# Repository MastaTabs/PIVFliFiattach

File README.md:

# PIV FlickerFixer attachment

This is a recreation from original data of the small snap off PCB of the PicassoIV (PIV)
Amiga RTG graphics card.
I created this because often cards seem to be sold without this PCB and then the FlickerFixer/ScanDoubler
of the card cannot be used.

This is a four layer PCB.

### License
The "PIV FlickerFixer attachment" documentation, including the design itself, is copyright © MastaTabs (Tobias Seiler) 2020.

"PIV FlickerFixer attachment" is Open Hardware licensed under the CERN OHL v. 1.2.

You may redistribute and modify this documentation under the terms of the CERN OHL v.1.2. This documentation is distributed as is and WITHOUT ANY EXPRESS OR IMPLIED WARRANTIES whatsoever with respect to its functionality, operability or use, including, without limitation, any implied warranties OF MERCHANTABILITY, SATISFACTORY QUALITY, FITNESS FOR A PARTICULAR PURPOSE or infringement. We expressly disclaim any liability whatsoever for any direct, indirect, consequential, incidental or special damages, including, without limitation, lost revenues, lost profits, losses resulting from business interruption or loss of data, regardless of the form of action or legal theory under which the liability may be asserted, even if advised of the possibility or likelihood of such damages.

A copy of the full license is included in file LICENSE.pdf, please refer to it for applicable conditions. In order to properly deal with its terms, please see file LICENSE_HOWTO.pdf.

The contact points for information about manufactured Products (see section 4.2) are listed in file PRODUCT.md.

Any modifications made by Licensees (see section 3.4.b) shall be recorded in file CHANGES.md.

The Documentation Location of the original project is https://github.com/MastaTabs/PIVFliFiattach.

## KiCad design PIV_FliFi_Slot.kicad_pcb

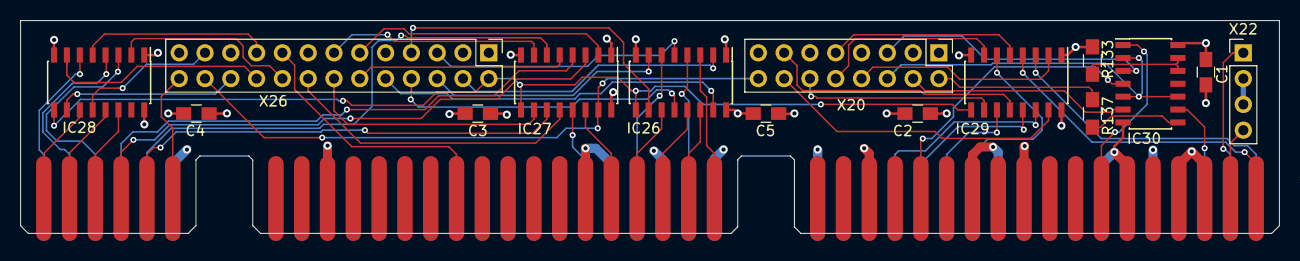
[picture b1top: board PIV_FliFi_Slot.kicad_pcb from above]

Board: 4 copper layers, 124.0 x 21.0 mm, 16 parts (0 on the bottom side), 64 nets.

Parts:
C1, C2, C3, C4, C5: C_Small; C_0805_HandSoldering
IC26, IC27, IC28, IC29: 74F378; SOIC-16_3.9x9.9mm_Pitch1.27mm
IC30: 74F32; SOIC-14_3.9x8.7mm_Pitch1.27mm
J1: VideoSlotMulti; VideoSlotMulti_Edge
R133, R137: R_Small; R_0805_HandSoldering
X20: Conn_02x08_Odd_Even; Pin_Header_Straight_2x08_Pitch2.54mm
X22: Conn_01x04; Pin_Header_Straight_1x04_Pitch2.54mm
X26: Conn_02x13_Odd_Even; Pin_Header_Straight_2x13_Pitch2.54mm

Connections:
+5V: C1.1, C2.1, C3.1, C4.1, C5.1, IC26.16, IC27.16, IC28.16, IC29.16, IC30.14, J1.6, J1.8, J1.35
/FF_SEL: J1.58, X26.17
/PB0: IC28.5, X26.19
/PB1: IC28.12, X26.23
/PB2: IC28.7, X26.20
/PB3: IC28.10, X26.22
/PB4: IC29.7, X20.10
/PB5: IC27.15, X20.16, X26.24
/PB6: IC27.12, X26.16
/PB7: IC29.10, X20.12
/PG0: IC27.5, X26.12
/PG1: IC27.2, X26.11
/PG2: IC28.2, X26.18
/PG4: IC26.12, X26.8
/PG5: IC26.7, X26.6
/PG6: IC26.10, X26.7
/PG7: IC29.12, X20.13
/PR0: IC29.2, X20.8
/PR1: IC29.5, X20.9
/PR2: IC27.7, X26.13
/PR3: IC27.10, X26.14
/PR4: IC26.2, X26.4
/PR5: IC26.5, X26.5
/PR6: IC26.15, X26.10
/PR7: IC29.15, X20.14
/Z28: IC30.9, J1.5
/ZB0: IC28.4, J1.81
/ZB1: IC28.13, J1.82
/ZB2: IC28.6, J1.83
/ZB3: IC28.11, J1.84
/ZB4: IC29.6, J1.23
/ZB5: IC27.14, J1.46
/ZB6: IC27.13, J1.47
/ZB7: IC29.11, J1.25
/ZBL: IC30.4, J1.28
/ZCS: IC30.1, J1.14
/ZG0: IC27.4, J1.77
/ZG1: IC27.3, J1.78
/ZG2: IC28.3, J1.79
/ZG3: IC28.14, J1.80
/ZG4: IC26.13, J1.42
/ZG5: IC26.6, J1.43
/ZG6: IC26.11, J1.44
/ZG7: IC29.13, J1.27
/ZR0: IC29.3, J1.1
/ZR1: IC29.4, J1.2
/ZR2: IC27.6, J1.75
/ZR3: IC27.11, J1.76
/ZR4: IC26.3, J1.38
/ZR5: IC26.4, J1.39
/ZR6: IC26.14, J1.40
/ZR7: IC29.14, J1.29
/ZVS2: J1.74, X26.26
GND: C1.2, C2.2, C3.2, C4.2, C5.2, IC26.1, IC26.8, IC27.1, IC27.8, IC28.1, IC28.8, IC29.1, IC29.8, IC30.7, J1.9, J1.12, J1.13, J1.20, J1.21, J1.24, J1.32, J1.37, J1.41, J1.45, J1.48, J1.68, J1.73, R133.1, X20.1, X20.3, X20.7, X20.11, X20.15, X26.1, X26.3, X26.9, X26.15, X26.21, X26.25
unnamed: IC26.9, IC27.9, IC28.9, IC29.9, X26.2
unnamed: IC30.3, X20.5
unnamed: IC30.6, X20.4
unnamed: IC30.8, R137.2
unnamed: IC30.2, IC30.5, IC30.10, X20.6
unnamed: IC30.12, IC30.13, R133.2
unnamed: J1.3, X22.1
unnamed: J1.4, X22.4
unnamed: R137.1, X20.2
unnamed: X22.2, X22.3

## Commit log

2020-05-28 fixed picture link
2020-05-28 added LICENSE file
2020-05-30 add License pdf's
2020-05-30 updated BOM
2020-05-30 cleanup
